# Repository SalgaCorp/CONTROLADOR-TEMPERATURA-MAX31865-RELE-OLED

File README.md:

# CONTROLADOR-TEMPERATURA-MAX31865-RELE-OLED

# Objetivos:

1.- Open Source.

2.- Control de temperatura de aceite por medio de un ESP32  .

3.- Varias entradas y dos relés: voltaje, %carga, etc.

# Contenido del repositorio:

PCB Datasheet Fotos

# Documentation:

Usa los siguientes componentes importantes:

MAX31865

(De Adafruit)
 
[MAX31865.pdf](https://github.com/SalgaCorp/CONTROLADOR-TEMPERATURA-MAX31865-RELE-OLED/files/10972528/MAX31865.pdf)

El módulo MAX31865 se puede configurar para trabajar con sensores PT100 de 2, 3 o 4 hilos. La configuración por defecto es para sensores de 4 hilos. 

El Módulo transmisor MAX31865 permite obtener de forma sencilla y confiable las mediciones de temperatura de los sensores RTD PT100. El módulo se encarga de realizar la lectura de resistencia del sensor PT100 y convertir esta señal analógica en un dato digital para ser interpretado por un microcontrolador. El chip MAX31865 posee un conversor ADC delta-sigma de precisión con una resolución de 15 bits, equivalente a 0.03125ºC. El protocolo de comunicación o interfaz es de tipo SPI.

El módulo está configurado por defecto para sensores PT100, por lo que el valor de Rref es de 430 Ohm. Para trabajar con sensores PT1000 debemos cambiar la resistencia de 430 Ohm por una de 4.3K Ohm.

# Enlaces y librerias:

https://github.com/adafruit/Adafruit_MAX31865

https://learn.adafruit.com/adafruit-max31865-rtd-pt100-amplifier?view=all

# Contact Us

Call or WhatsApp 

https://api.whatsapp.com/send?phone=56966814899

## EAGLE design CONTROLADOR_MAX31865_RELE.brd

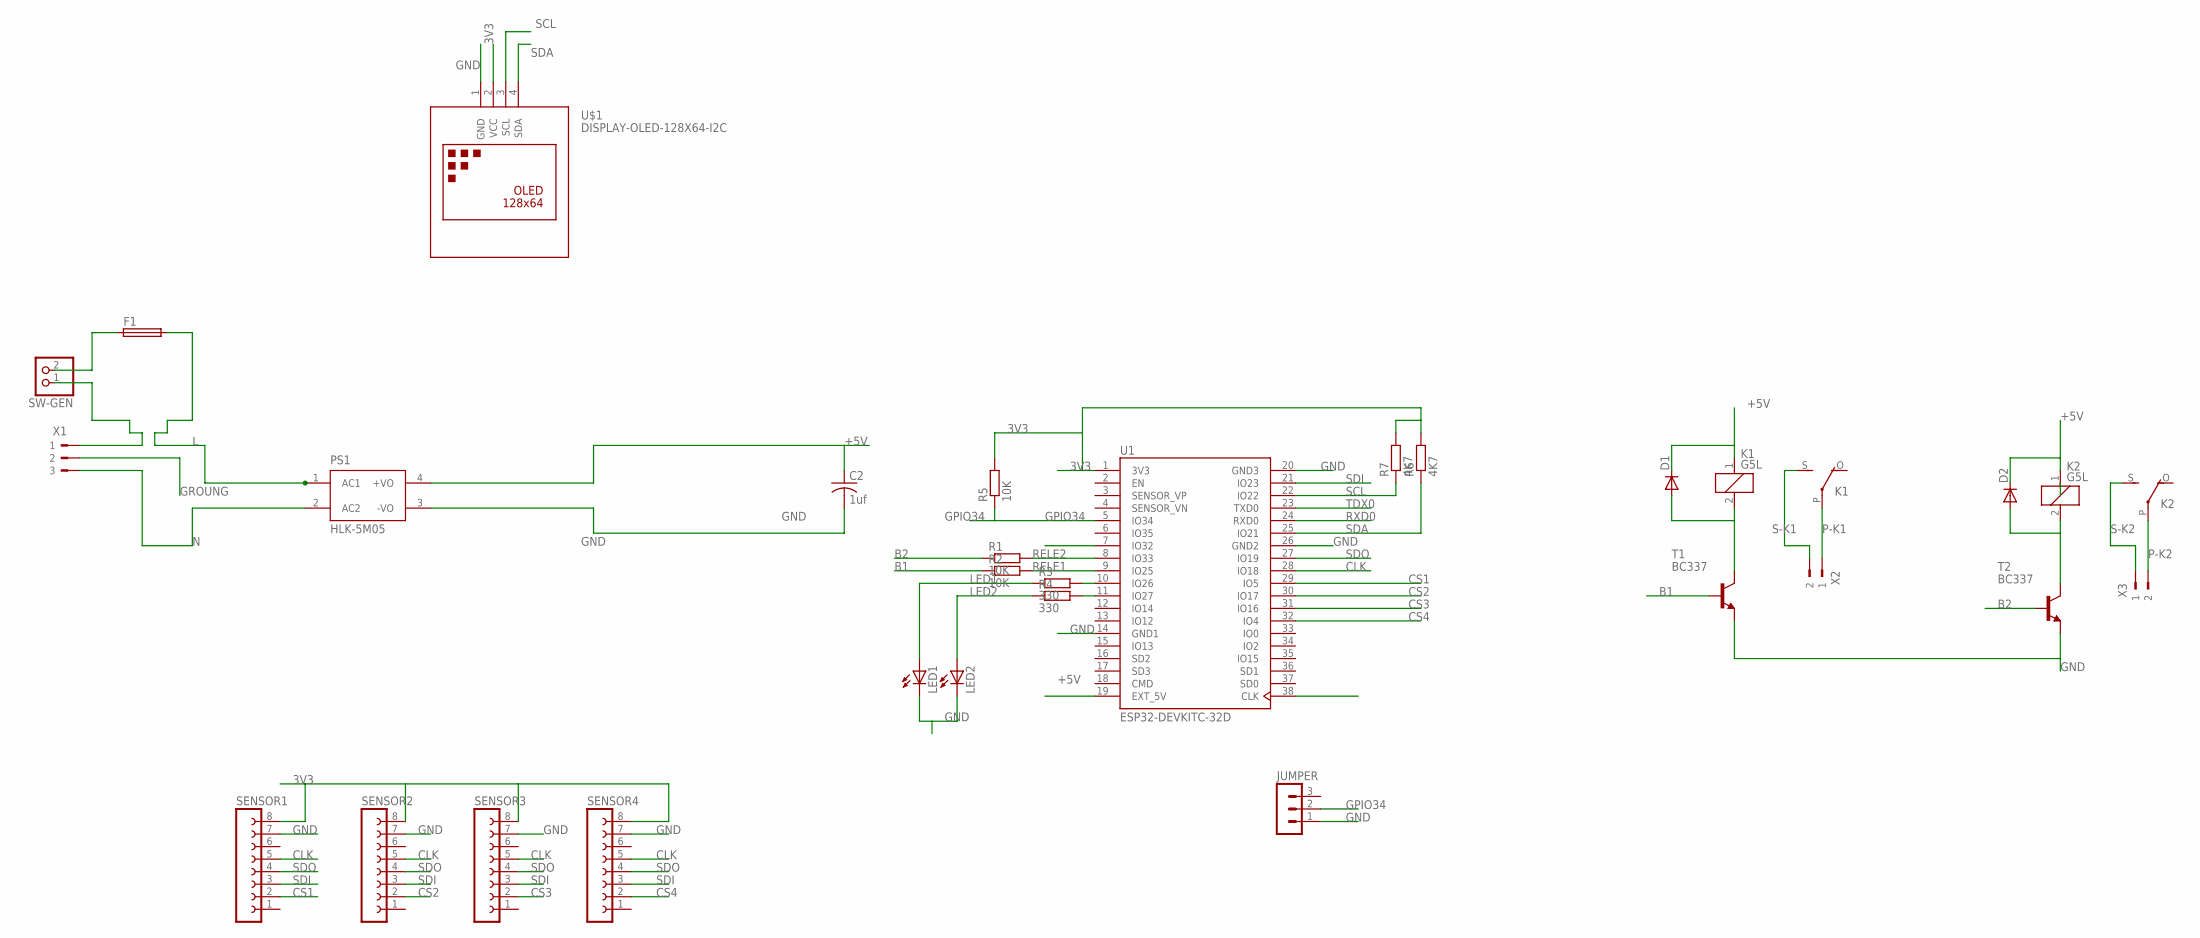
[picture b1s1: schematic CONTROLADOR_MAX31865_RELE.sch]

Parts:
C2: 1uf; C1206
D1, D2: DIODE-DO214AC; DO214AC
F1: SH22,5A
JUMPER: MA03-1
K1, K2: G5L; G5LE
LED1, LED2: LED3MM
PS1: HLK-5M05; CONV_HLK-5M05
R1, R2, R5: 10K; M1206
R3, R4: 330; M1206
R6, R7: 4K7; M1206
SENSOR1, SENSOR2, SENSOR3, SENSOR4: FE08-1; FE08
SW-GEN: PINHD-1X2; 1X02
T1, T2: BC337; TO92
U1: ESP32-DEVKITC-32D; MODULE_ESP32-DEVKITC-32D
U$1: DISPLAY-OLED-128X64-I2C
X1: 180G-3
X2, X3: 90-2

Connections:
3V3: R5.2, R6.2, R7.2, SENSOR1.8, SENSOR2.8, SENSOR3.8, SENSOR4.8, U1.1 (3V3), U$1.2 (VCC)
+5V: C2.1, D1.C, D2.C, K1.1, K2.1, PS1.4 (+VO), U1.19 (EXT_5V)
B1: R2.1, T1.2 (B)
B2: R1.1, T2.2 (B)
CCLK: U1.38 (CLK)
CLK: SENSOR1.5, SENSOR2.5, SENSOR3.5, SENSOR4.5, U1.28 (IO18)
CS1: SENSOR1.2, U1.29 (IO5)
CS2: SENSOR2.2, U1.30 (IO17)
CS3: SENSOR3.2, U1.31 (IO16)
CS4: SENSOR4.2, U1.32 (IO4)
GND: C2.2, JUMPER.1, LED1.K (C), LED2.K (C), PS1.3 (-VO), SENSOR1.7, SENSOR2.7, SENSOR3.7, SENSOR4.7, T1.1 (E), T2.1 (E), U1.14 (GND1), U1.20 (GND3), U1.26 (GND2), U$1.1 (GND)
GPIO34: JUMPER.2, R5.1, U1.5 (IO34)
GROUNG: X1.2
L: F1.2, PS1.1 (AC1)
L.: SW-GEN.1, X1.1
LED1: LED1.A, R3.1
LED2: LED2.A, R4.1
N: PS1.2 (AC2), X1.3
unnamed: F1.1, SW-GEN.2
unnamed: R3.2, U1.10 (IO26)
unnamed: R4.2, U1.11 (IO27)
unnamed: D1.A, K1.2, T1.3 (C)
unnamed: D2.A, K2.2, T2.3 (C)
P-K1: K1.P, X2.1
P-K2: K2.P, X3.2
RELE1: R2.2, U1.9 (IO25)
RELE2: R1.2, U1.8 (IO33)
RXD0: U1.24 (RXD0)
S-K1: K1.S, X2.2
S-K2: K2.S, X3.1
SCL: R7.1, U1.22 (IO22), U$1.3 (SCL)
SDA: R6.1, U1.25 (IO21), U$1.4 (SDA)
SDI: SENSOR1.3, SENSOR2.3, SENSOR3.3, SENSOR4.3, U1.21 (IO23)
SDO: SENSOR1.4, SENSOR2.4, SENSOR3.4, SENSOR4.4, U1.27 (IO19)
TDX0: U1.23 (TXD0)

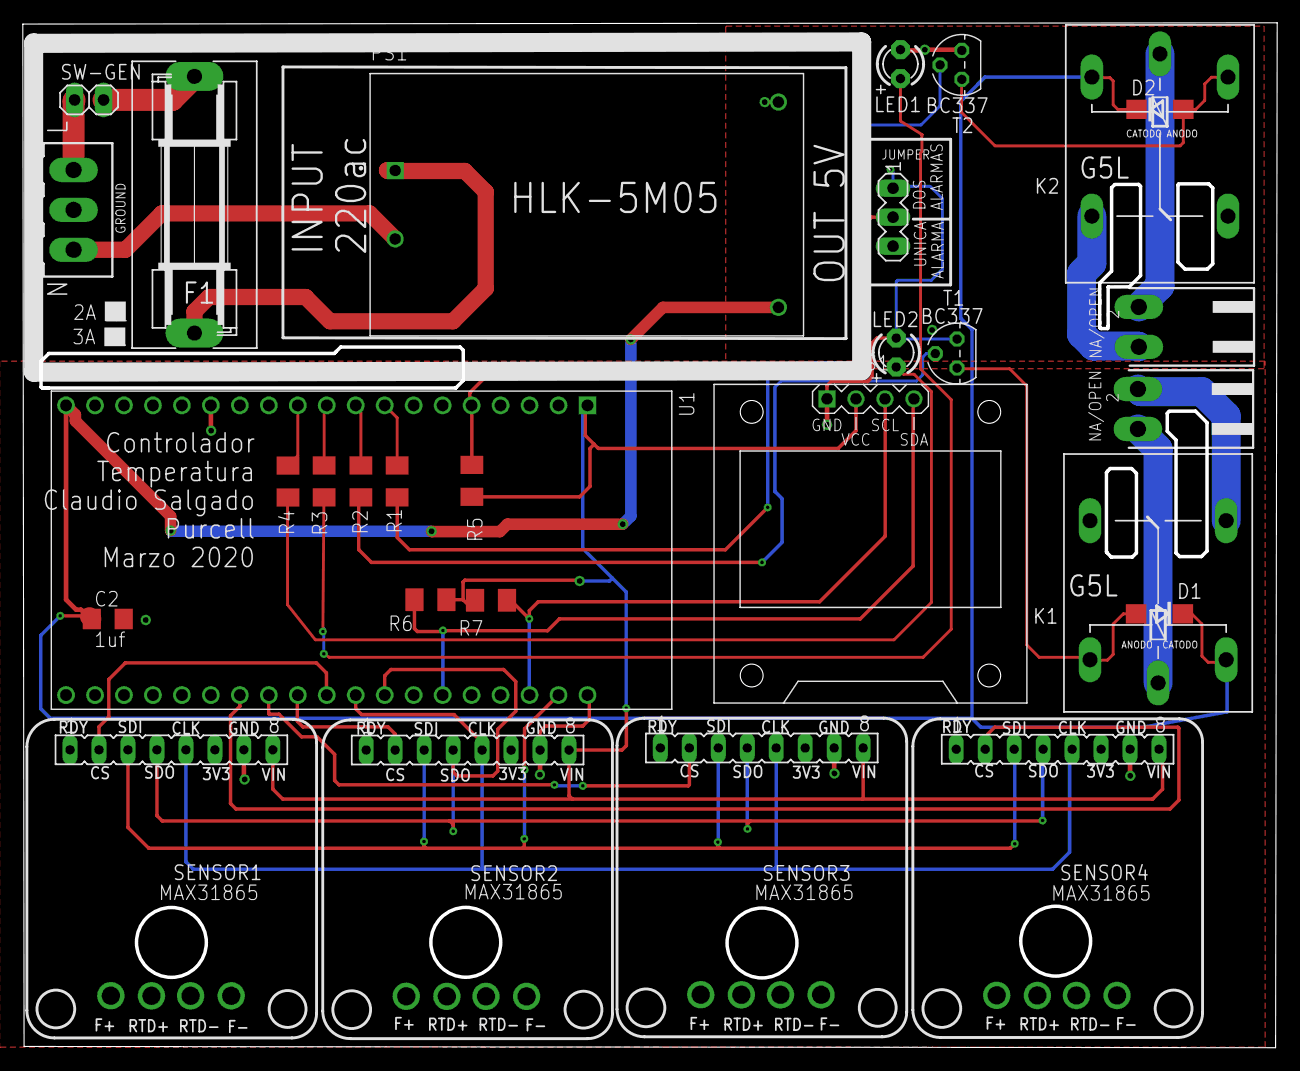
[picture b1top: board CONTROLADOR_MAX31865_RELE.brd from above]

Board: 2 copper layers, 109.7 x 89.6 mm, 29 parts (0 on the bottom side), 31 nets.

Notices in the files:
parts and their libraries:
cargador microusb-modules lib: Released under the Creative Commons Attribution 4.0 International License: http://creativecommons.org/licenses/by/4.0
